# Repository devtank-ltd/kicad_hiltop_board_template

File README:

Copyright Devtank Ltd 2022.

This documentation describes Open Hardware and is Licensed under CERN-OHL-W v2.

You may redistribute and modify this documentation under the terms of the CERN-OHL-W v2 (https://cern.ch/cern-ohl). This documentation is distributed WITHOUT ANY EXPRESS OR IMPLIED WARRANTY, INCLUDING OF MERCHANTABILITY, SATISFACTORY QUALITY AND FITNESS FOR A PARTICULAR PURPOSE. Please see the CERN-OHL-W v2 for applicable conditions

Source location: git@github.com:devtank-ltd/hiltop_motherboard.git 

As per CERN-OHL-W v2 section 4.1, should You produce hardware based on these sources, You must maintain the   Source Location visible on the external case of the HILTOP or other product you make using this documentation.

This folder contains a reference HILTOP plug-in card design schematics & PCB layout. You may use this design as a starting template for developing new plug-in modules for HILTOP.

You will need Kicad to open hardware design files.

HILTOP products and other test and measurement solutions can be purchased directly from Devtank Ltd.

Please contact:
Tim Telford
CTO - Devtank Ltd
+44 (0)1332 650944

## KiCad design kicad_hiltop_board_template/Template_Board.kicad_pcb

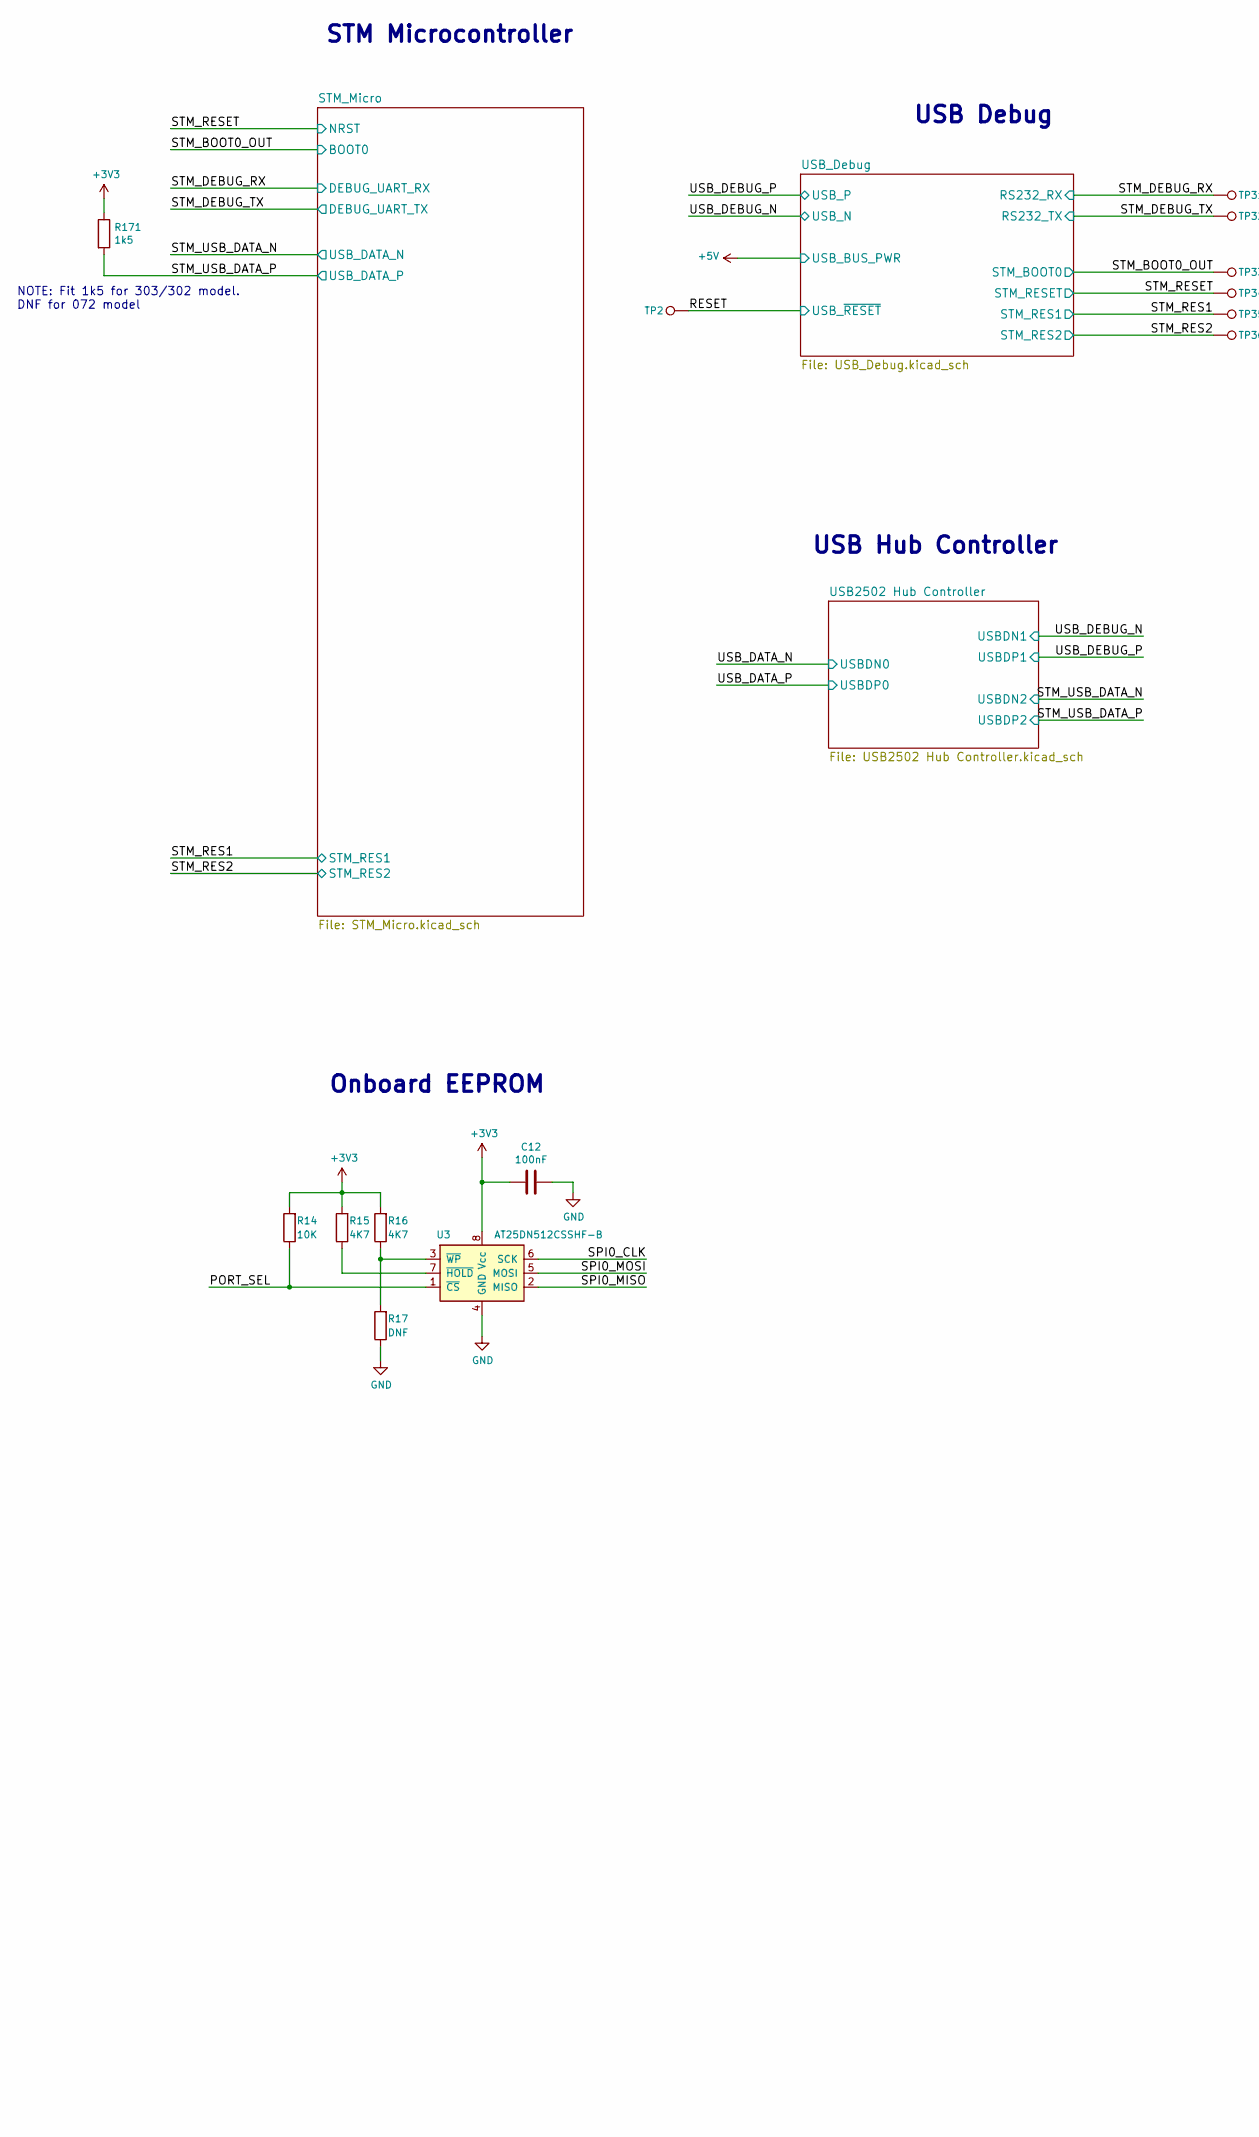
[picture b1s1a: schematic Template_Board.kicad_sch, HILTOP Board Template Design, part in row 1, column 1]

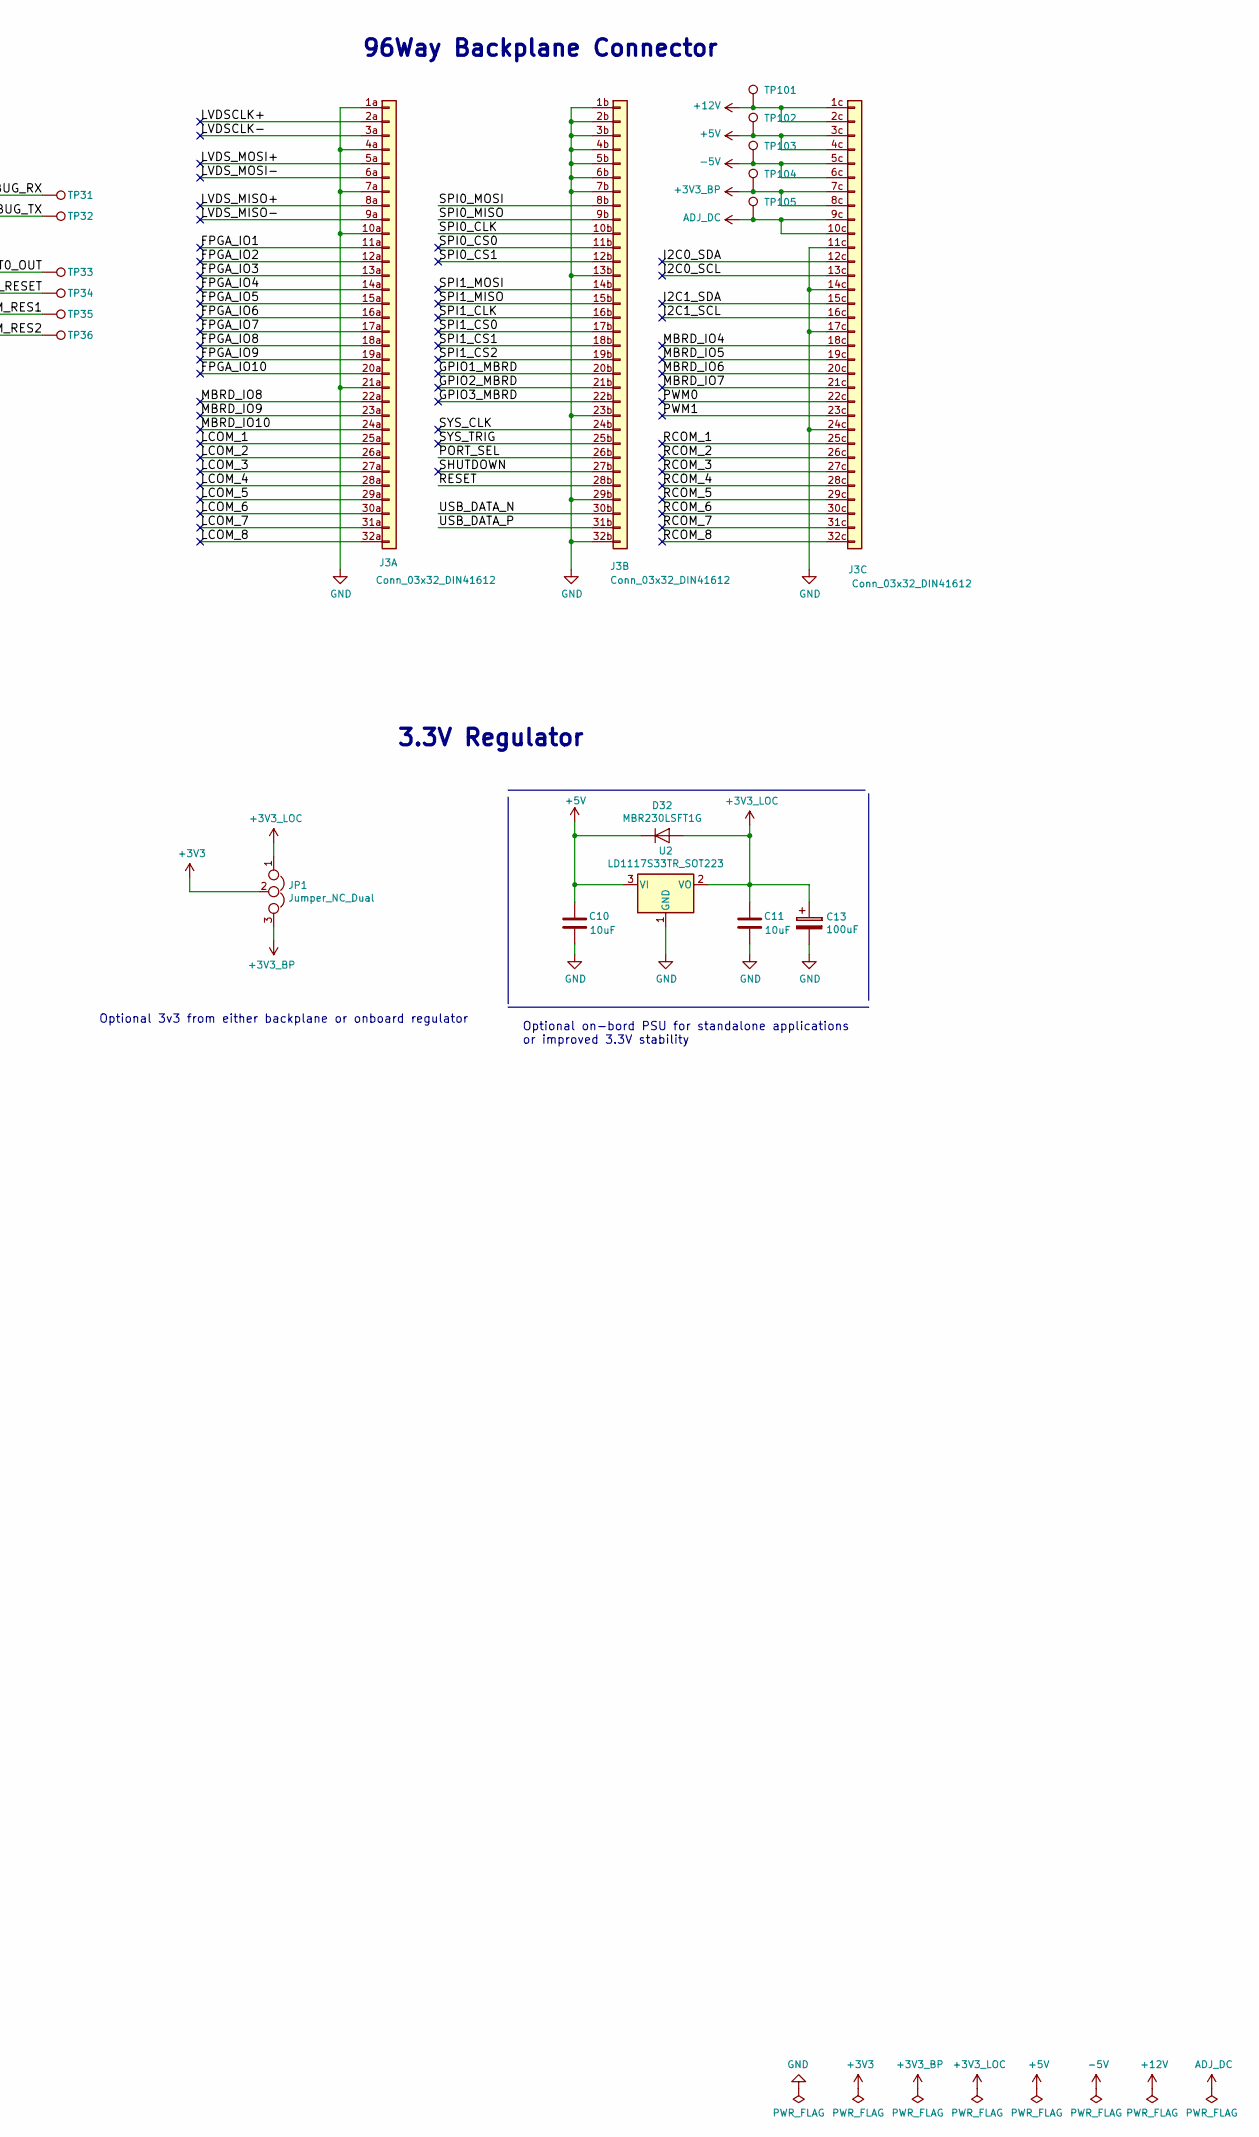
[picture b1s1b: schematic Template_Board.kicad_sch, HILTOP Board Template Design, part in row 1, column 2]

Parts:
C10, C11: 10uF; C_0805_2012Metric
C12: 100nF; C_0402_1005Metric
C13: 100uF; CP_Elec_6.3x7.7
D32: MBR230LSFT1G; D_SOD-123
J3: Conn_03x32_DIN41612; Socket_DIN41612-CaseC1-full-Male-96Pin-3rows_correct
JP1: Jumper_NC_Dual; PinHeader_1x03_P2.54mm_Vertical
R14: 10K; R_0603_1608Metric
R15, R16: 4K7; R_0603_1608Metric
R17: DNF; R_0603_1608Metric
R171: 1k5; R_0603_1608Metric
TP2, TP31, TP32, TP33, TP34, TP35, TP36, TP101, TP102, TP103, TP104, TP105: Test_Point; TestPoint_THTPad_D1.0mm_Drill0.5mm
U2: LD1117S33TR_SOT223; SOT-223-3_TabPin2
U3: AT25DN512CSSHF-B; SOIC-8_3.9x4.9mm_P1.27mm

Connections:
+3V3: C12.2, JP1.2, R14.2, R15.2, R16.2, R171.1, U3.8 (Vcc); also elsewhere on the board
+3V3_BP: J3.7c (Pin_7), J3.8c (Pin_8), JP1.3, TP104.1
+3V3_LOC: C11.2, C13.1, D32.2 (A), JP1.1, U2.2 (VO)
+5V: C10.2, D32.1 (K), J3.3c (Pin_3), J3.4c (Pin_4), TP102.1, U2.3 (VI); also elsewhere on the board
+12V: J3.1c (Pin_1), J3.2c (Pin_2), TP101.1
-5V: J3.5c (Pin_5), J3.6c (Pin_6), TP103.1
/FPGA_IO1: J3.11a (Pin_11)
/FPGA_IO2: J3.12a (Pin_12)
/FPGA_IO3: J3.13a (Pin_13)
/FPGA_IO4: J3.14a (Pin_14)
/FPGA_IO5: J3.15a (Pin_15)
/FPGA_IO6: J3.16a (Pin_16)
/FPGA_IO7: J3.17a (Pin_17)
/FPGA_IO8: J3.18a (Pin_18)
/FPGA_IO9: J3.19a (Pin_19)
/FPGA_IO10: J3.20a (Pin_20)
/GPIO1_MBRD: J3.20b (Pin_20)
/GPIO2_MBRD: J3.21b (Pin_21)
/GPIO3_MBRD: J3.22b (Pin_22)
/I2C0_SCL: J3.13c (Pin_13)
/I2C0_SDA: J3.12c (Pin_12)
/I2C1_SCL: J3.16c (Pin_16)
/I2C1_SDA: J3.15c (Pin_15)
/LCOM_1: J3.25a (Pin_25)
/LCOM_2: J3.26a (Pin_26)
/LCOM_3: J3.27a (Pin_27)
/LCOM_4: J3.28a (Pin_28)
/LCOM_5: J3.29a (Pin_29)
/LCOM_6: J3.30a (Pin_30)
/LCOM_7: J3.31a (Pin_31)
/LCOM_8: J3.32a (Pin_32)
/LVDSCLK+: J3.2a (Pin_2)
/LVDSCLK-: J3.3a (Pin_3)
/LVDS_MISO+: J3.8a (Pin_8)
/LVDS_MISO-: J3.9a (Pin_9)
/LVDS_MOSI+: J3.5a (Pin_5)
/LVDS_MOSI-: J3.6a (Pin_6)
/MBRD_IO4: J3.18c (Pin_18)
/MBRD_IO5: J3.19c (Pin_19)
/MBRD_IO6: J3.20c (Pin_20)
/MBRD_IO7: J3.21c (Pin_21)
/MBRD_IO8: J3.22a (Pin_22)
/MBRD_IO9: J3.23a (Pin_23)
/MBRD_IO10: J3.24a (Pin_24)
/PORT_SEL: J3.26b (Pin_26), R14.1, U3.1 (~CS)
/PWM0: J3.22c (Pin_22)
/PWM1: J3.23c (Pin_23)
/RCOM_1: J3.25c (Pin_25)
/RCOM_2: J3.26c (Pin_26)
/RCOM_3: J3.27c (Pin_27)
/RCOM_4: J3.28c (Pin_28)
/RCOM_5: J3.29c (Pin_29)
/RCOM_6: J3.30c (Pin_30)
/RCOM_7: J3.31c (Pin_31)
/RCOM_8: J3.32c (Pin_32)
/RESET: J3.28b (Pin_28), TP2.1; also elsewhere on the board
/SHUTDOWN: J3.27b (Pin_27)
/SPI0_CLK: J3.10b (Pin_10), U3.6 (SCK)
/SPI0_CS0: J3.11b (Pin_11)
/SPI0_CS1: J3.12b (Pin_12)
/SPI0_MISO: J3.9b (Pin_9), U3.2 (MISO)
/SPI0_MOSI: J3.8b (Pin_8), U3.5 (MOSI)
/SPI1_CLK: J3.16b (Pin_16)
/SPI1_CS0: J3.17b (Pin_17)
/SPI1_CS1: J3.18b (Pin_18)
/SPI1_CS2: J3.19b (Pin_19)
/SPI1_MISO: J3.15b (Pin_15)
/SPI1_MOSI: J3.14b (Pin_14)
/STM_BOOT0_OUT: TP33.1; also elsewhere on the board
/STM_DEBUG_RX: TP31.1; also elsewhere on the board
/STM_DEBUG_TX: TP32.1; also elsewhere on the board
/STM_RES1: TP35.1; also elsewhere on the board
/STM_RES2: TP36.1; also elsewhere on the board
/STM_RESET: TP34.1; also elsewhere on the board
/STM_USB_DATA_P: R171.2; also elsewhere on the board
/SYS_CLK: J3.24b (Pin_24)
/SYS_TRIG: J3.25b (Pin_25)
/USB_DATA_N: J3.30b (Pin_30); also elsewhere on the board
/USB_DATA_P: J3.31b (Pin_31); also elsewhere on the board
ADJ_DC: J3.9c (Pin_9), J3.10c (Pin_10), TP105.1
GND: C10.1, C11.1, C12.1, C13.2, J3.1a (Pin_1), J3.1b (Pin_1), J3.2b (Pin_2), J3.3b (Pin_3), J3.4a (Pin_4), J3.4b (Pin_4), J3.5b (Pin_5), J3.6b (Pin_6), J3.7a (Pin_7), J3.7b (Pin_7), J3.10a (Pin_10), J3.11c (Pin_11), J3.13b (Pin_13), J3.14c (Pin_14), J3.17c (Pin_17), J3.21a (Pin_21), J3.23b (Pin_23), J3.24c (Pin_24), J3.29b (Pin_29), J3.32b (Pin_32), R17.1, U2.1 (GND), U3.4 (GND); also elsewhere on the board
unnamed: R15.1, U3.7 (~HOLD)
unnamed: R16.1, R17.2, U3.3 (~WP)

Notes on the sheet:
USB Debug
96Way Backplane Connector
Optional on-bord PSU for standalone applications or improved 3.3V stability
Onboard EEPROM
USB Hub Controller
NOTE: Fit 1k5 for 303/302 model. DNF for 072 model
STM Microcontroller
Optional 3v3 from either backplane or onboard regulator
3.3V Regulator

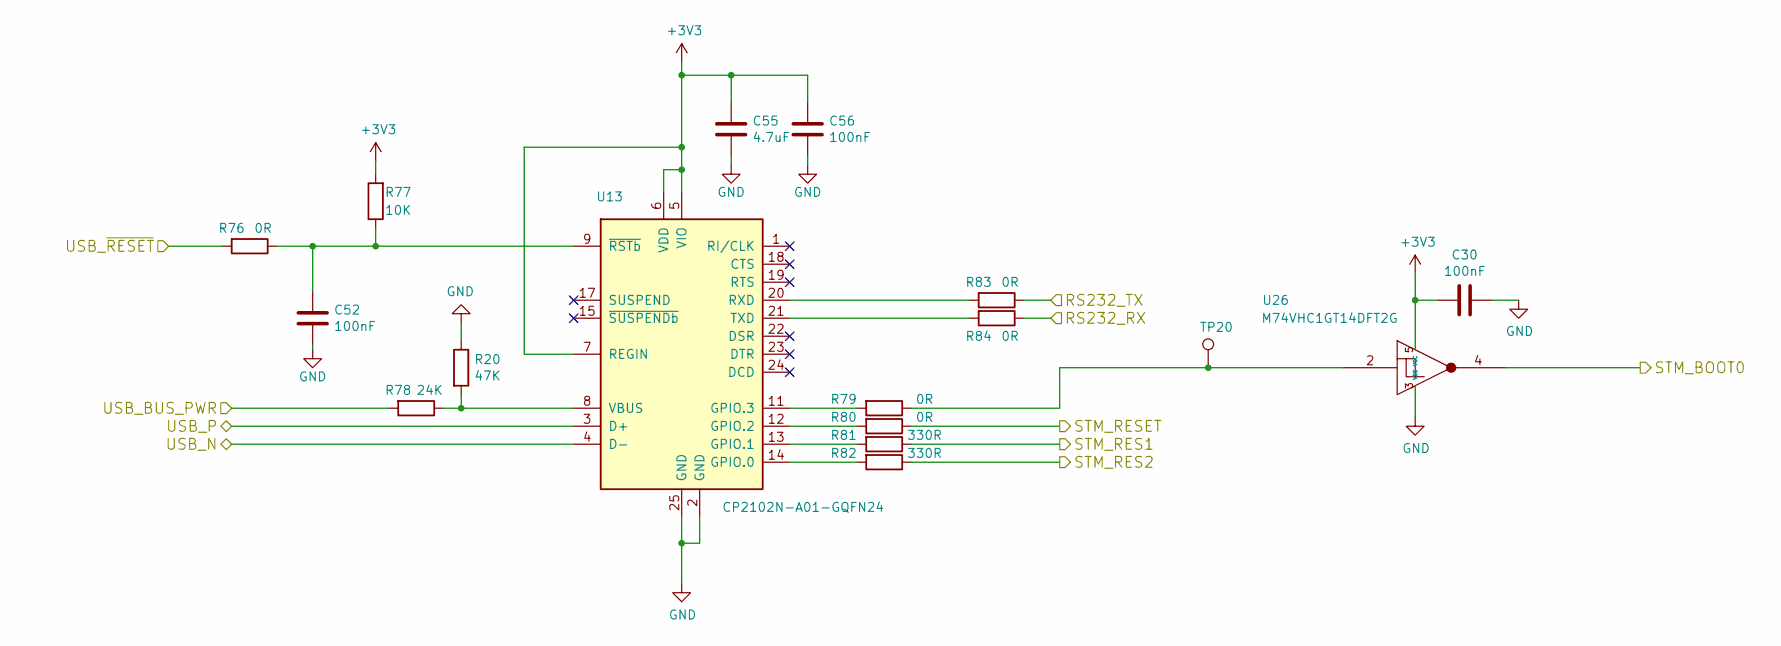
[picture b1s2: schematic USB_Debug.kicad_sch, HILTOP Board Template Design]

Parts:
C30, C56: 100nF; C_0402_1005Metric
C52: 100nF; C_0603_1608Metric
C55: 4.7uF; C_0402_1005Metric; Voltage 6.3V
R20: 47K; R_0603_1608Metric
R76, R79, R80, R83, R84: 0R; R_0603_1608Metric
R77: 10K; R_0603_1608Metric
R78: 24K; R_0603_1608Metric
R81, R82: 330R; R_0603_1608Metric
TP20: Test_Point; TestPoint_THTPad_D1.0mm_Drill0.5mm
U13: CP2102N-A01-GQFN24; CP2102_QFN-24-1EP_4x4mm_P0.5mm_EP2.6x2.6mm_ThermalVias_0.3m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
U26: M74VHC1GT14DFT2G; SOT-353_SC-70-5

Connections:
+3V3: C30.2, C55.1, C56.1, R77.2, U13.5 (VIO), U13.6 (VDD), U13.7 (REGIN), U26.5 (VCC); also elsewhere on the board
+5V: R78.2; also elsewhere on the board
/RESET: R76.2; also elsewhere on the board
/STM_BOOT0_OUT: U26.4; also elsewhere on the board
/STM_DEBUG_RX: R84.1; also elsewhere on the board
/STM_DEBUG_TX: R83.1; also elsewhere on the board
/STM_RES1: R81.1; also elsewhere on the board
/STM_RES2: R82.1; also elsewhere on the board
/STM_RESET: R80.1; also elsewhere on the board
/USB_DEBUG_N: U13.4 (D-); also elsewhere on the board
/USB_DEBUG_P: U13.3 (D+); also elsewhere on the board
GND: C30.1, C52.2, C55.2, C56.2, R20.1, U13.2 (GND), U13.25 (GND), U26.3 (VSS); also elsewhere on the board
unnamed: C52.1, R76.1, R77.1, U13.9 (~RSTb)
unnamed: R20.2, R78.1, U13.8 (VBUS)
unnamed: R79.1, TP20.1, U26.2
unnamed: R79.2, U13.11 (GPIO.3)
unnamed: R80.2, U13.12 (GPIO.2)
unnamed: R81.2, U13.13 (GPIO.1)
unnamed: R82.2, U13.14 (GPIO.0)
unnamed: R83.2, U13.20 (RXD)
unnamed: R84.2, U13.21 (TXD)

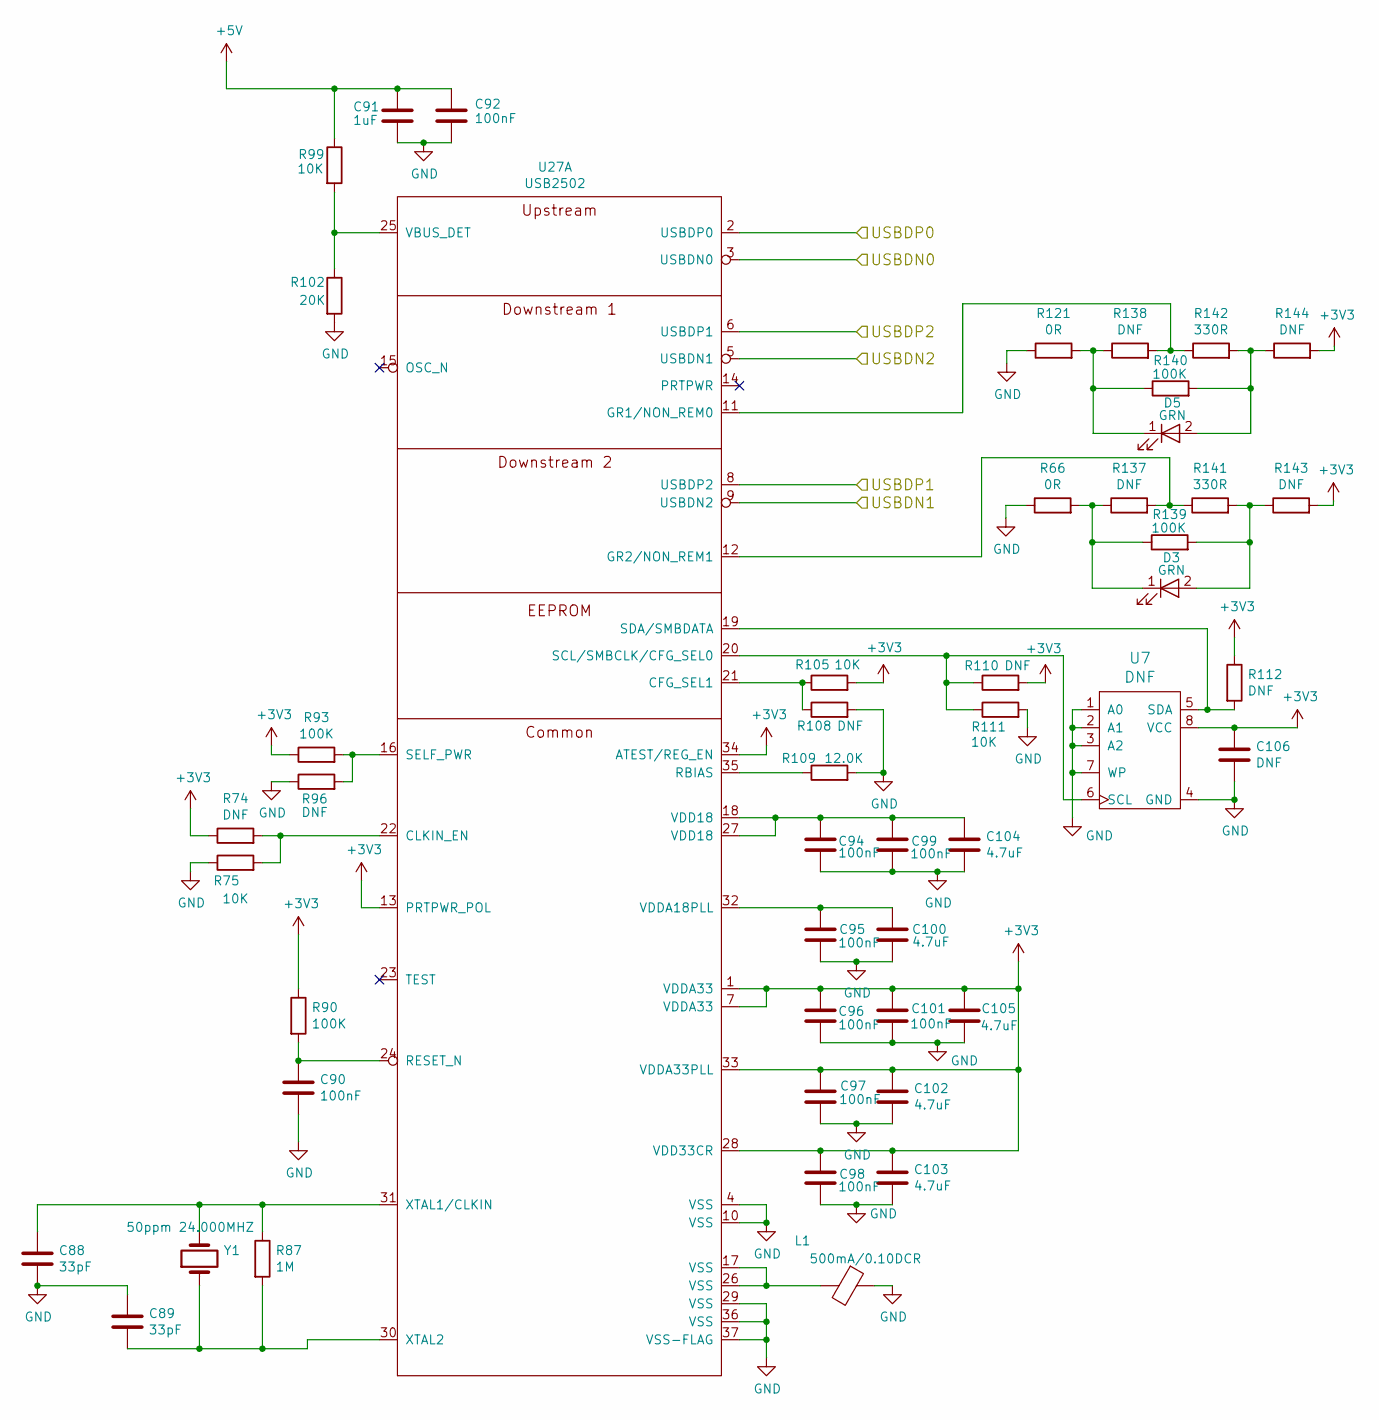
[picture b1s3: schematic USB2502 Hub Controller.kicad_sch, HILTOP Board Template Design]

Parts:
C88, C89: 33pF; C_0603_1608Metric
C90: 100nF; C_0603_1608Metric
C91: 1uF; C_0402_1005Metric; Voltage 16V
C92, C94, C95, C96, C97, C98, C99, C101: 100nF; C_0402_1005Metric
C100, C102, C103, C104, C105: 4.7uF; C_0402_1005Metric; Voltage 6.3V
C106: DNF; C_0402_1005Metric
D3, D5: GRN; LED_0603_1608Metric
L1: 500mA/0.10DCR; L_0805_2012Metric
R66, R121: 0R; R_0603_1608Metric
R74, R96, R108, R110, R112, R137, R138, R143, R144: DNF; R_0603_1608Metric
R75, R99, R105, R111: 10K; R_0603_1608Metric
R87: 1M; R_0603_1608Metric
R90, R93, R139, R140: 100K; R_0603_1608Metric
R102: 20K; R_0603_1608Metric
R109: 12.0K; R_0603_1608Metric; Tolerance 1%
R141, R142: 330R; R_0603_1608Metric
U7: DNF; SOIC-8_3.9x4.9mm_P1.27mm
U27: USB2502; QFN-36-1EP_6x6mm_P0.5mm_EP3.7x3.7mm
Y1: 50ppm 24.000MHZ; Crystal_SMD_TXC_7A-2Pin_5x3.2mm

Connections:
+3V3: C96.1, C97.1, C98.1, C101.1, C102.1, C103.1, C105.1, C106.1, R74.1, R90.1, R93.1, R105.2, R110.2, R112.1, R143.2, R144.2, U7.8 (VCC), U27.1 (VDDA33), U27.7 (VDDA33), U27.13 (PRTPWR_POL), U27.28 (VDD33CR), U27.33 (VDDA33PLL), U27.34 (ATEST/REG_EN); also elsewhere on the board
+5V: C91.1, C92.1, R99.1; also elsewhere on the board
/STM_USB_DATA_N: U27.5 (USBDN1); also elsewhere on the board
/STM_USB_DATA_P: U27.6 (USBDP1); also elsewhere on the board
/USB_DATA_N: U27.3 (USBDN0); also elsewhere on the board
/USB_DATA_P: U27.2 (USBDP0); also elsewhere on the board
/USB_DEBUG_N: U27.9 (USBDN2); also elsewhere on the board
/USB_DEBUG_P: U27.8 (USBDP2); also elsewhere on the board
GND: C88.2, C89.1, C90.2, C91.2, C92.2, C94.2, C95.2, C96.2, C97.2, C98.2, C99.2, C100.2, C101.2, C102.2, C103.2, C104.2, C105.2, C106.2, L1.1, R66.1, R75.1, R96.1, R102.2, R108.2, R109.2, R111.2, R121.1, U7.1 (A0), U7.2 (A1), U7.3 (A2), U7.4 (GND), U7.7 (WP), U27.4 (VSS), U27.10 (VSS), U27.29 (VSS), U27.36 (VSS), U27.37 (VSS-FLAG); also elsewhere on the board
unnamed: C88.1, R87.1, U27.31 (XTAL1/CLKIN), Y1.2
unnamed: C89.2, R87.2, U27.30 (XTAL2), Y1.1
unnamed: C90.1, R90.2, U27.24 (RESET_N)
unnamed: C95.1, C100.1, U27.32 (VDDA18PLL)
unnamed: C94.1, C99.1, C104.1, U27.18 (VDD18), U27.27 (VDD18)
unnamed: D3.1 (K), R66.2, R137.1, R139.1
unnamed: D3.2 (A), R139.2, R141.2, R143.1
unnamed: D5.1 (K), R121.2, R138.1, R140.1
unnamed: D5.2 (A), R140.2, R142.2, R144.1
unnamed: L1.2, U27.17 (VSS), U27.26 (VSS)
unnamed: R74.2, R75.2, U27.22 (CLKIN_EN)
unnamed: R93.2, R96.2, U27.16 (SELF_PWR)
unnamed: R99.2, R102.1, U27.25 (VBUS_DET)
unnamed: R105.1, R108.1, U27.21 (CFG_SEL1)
unnamed: R109.1, U27.35 (RBIAS)
unnamed: R110.1, R111.1, U7.6 (SCL), U27.20 (SCL/SMBCLK/CFG_SEL0)
unnamed: R112.2, U7.5 (SDA), U27.19 (SDA/SMBDATA)
unnamed: R137.2, R141.1, U27.12 (GR2/NON_REM1)
unnamed: R138.2, R142.1, U27.11 (GR1/NON_REM0)

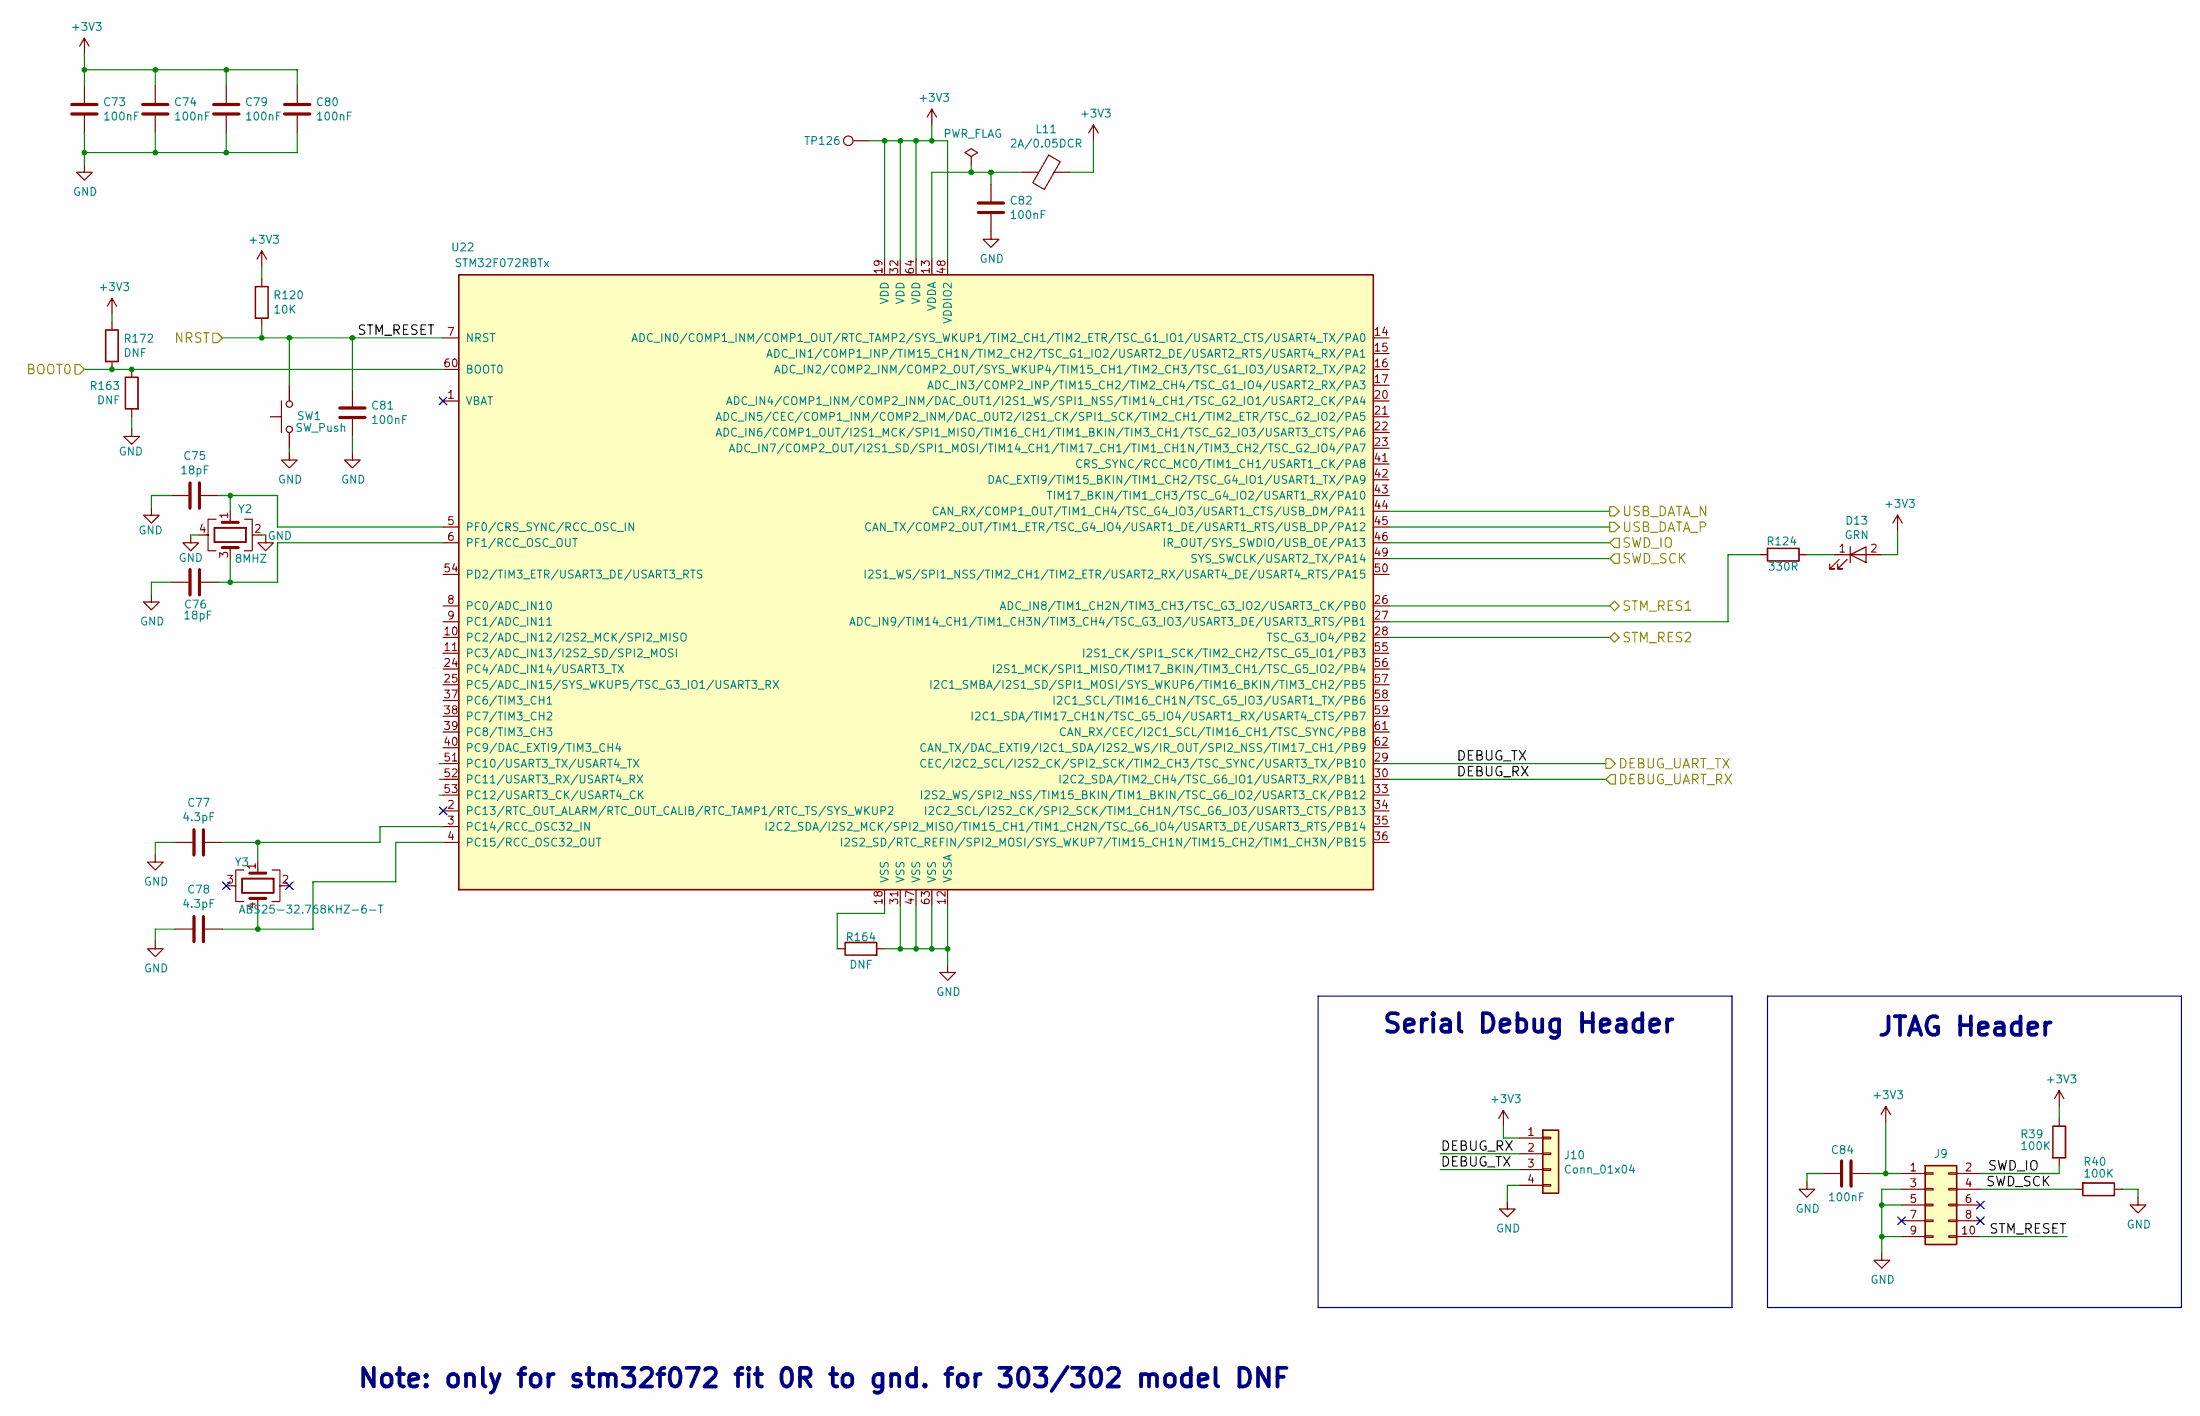
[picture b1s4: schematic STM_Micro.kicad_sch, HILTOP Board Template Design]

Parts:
C73, C74, C79, C80, C84: 100nF; C_0402_1005Metric
C75, C76: 18pF; C_0603_1608Metric
C77, C78: 4.3pF; C_0603_1608Metric
C81, C82: 100nF; C_0603_1608Metric
D13: GRN; LED_0603_1608Metric
J9: Conn_02x05_Odd_Even; PinHeader_2x05_P2.54mm_Vertical
J10: Conn_01x04; PinHeader_1x04_P1.27mm_Vertical
L11: 2A/0.05DCR; L_0805_2012Metric
R39, R40: 100K; R_0603_1608Metric
R120: 10K; R_0603_1608Metric
R124: 330R; R_0603_1608Metric
R163, R172: DNF; R_0603_1608Metric
R164: DNF; R_0402_1005Metric
SW1: SW_Push; SW_SPST_B3U-1000P
TP126: Test_Point; TestPoint_THTPad_D1.0mm_Drill0.5mm
U22: STM32F072RBTx; LQFP-64_10x10mm_P0.5mm
Y2: 8MHZ; Crystal_SMD_Abracon_ABM3C-4Pin_5.0x3.2mm
Y3: ABS25-32.768KHZ-6-T; Crystal_SMD_7050-4Pin_7.0x5.0mm

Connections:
+3V3: C73.1, C74.1, C79.1, C80.1, C84.2, D13.2 (A), J9.1, J10.1, L11.1, R39.1, R120.1, R172.1, TP126.1, U22.19 (VDD), U22.32 (VDD), U22.48 (VDDIO2), U22.64 (VDD); also elsewhere on the board
/STM_BOOT0_OUT: R163.1, R172.2, U22.60 (BOOT0); also elsewhere on the board
/STM_DEBUG_RX: J10.2, U22.30 (I2C2_SDA/TIM2_CH4/TSC_G6_IO1/USART3_RX/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); also elsewhere on the board
/STM_DEBUG_TX: J10.3, U22.29 (CEC/I2C2_SCL/I2S2_CK/SPI2_SCK/TIM2_CH3/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); also elsewhere on the board
/STM_Micro/SWD_IO: J9.2, R39.2, U22.46 (IR_OUT/SYS_SWDIO/USB_OE/PA13)
/STM_Micro/SWD_SCK: J9.4, R40.2, U22.49 (SYS_SWCLK/USART2_TX/PA14)
/STM_RES1: U22.26 (ADC_IN8/TIM1_CH2N/TIM3_CH3/TSC_G3_IO2/U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); also elsewhere on the board
/STM_RES2: U22.28 (TSC_G3_IO4/PB2); also elsewhere on the board
/STM_RESET: C81.1, J9.10, R120.2, SW1.2, U22.7 (NRST); also elsewhere on the board
/STM_USB_DATA_N: U22.44 (CAN_RX/COMP1_OUT/TIM1_CH4/TSC_G4_IO3/US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); also elsewhere on the board
/STM_USB_DATA_P: U22.45 (CAN_TX/COMP2_OUT/TIM1_ETR/TSC_G4_IO4/US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); also elsewhere on the board
GND: C73.2, C74.2, C75.2, C76.2, C77.2, C78.2, C79.2, C80.2, C81.2, C82.2, C84.1, J9.3, J9.5, J9.9, J10.4, R40.1, R163.2, R164.2, SW1.1, U22.12 (VSSA), U22.31 (VSS), U22.47 (VSS), U22.63 (VSS), Y2.2, Y2.4; also elsewhere on the board
unnamed: C75.1, U22.5 (PF0/CRS_SYNC/RCC_OSC_IN), Y2.1
unnamed: C76.1, U22.6 (PF1/RCC_OSC_OUT), Y2.3
unnamed: C77.1, U22.3 (PC14/RCC_OSC32_IN), Y3.1
unnamed: C78.1, U22.4 (PC15/RCC_OSC32_OUT), Y3.4
unnamed: C82.1, L11.2, U22.13 (VDDA)
unnamed: D13.1 (K), R124.1
unnamed: R124.2, U22.27 (ADC_IN9/TIM14_CH1/TIM1_CH3N/TIM3_CH4/TS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)
unnamed: R164.1, U22.18 (VSS)

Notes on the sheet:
JTAG Header
Note: only for stm32f072 fit 0R to gnd. for 303/302 model DNF
Serial Debug Header

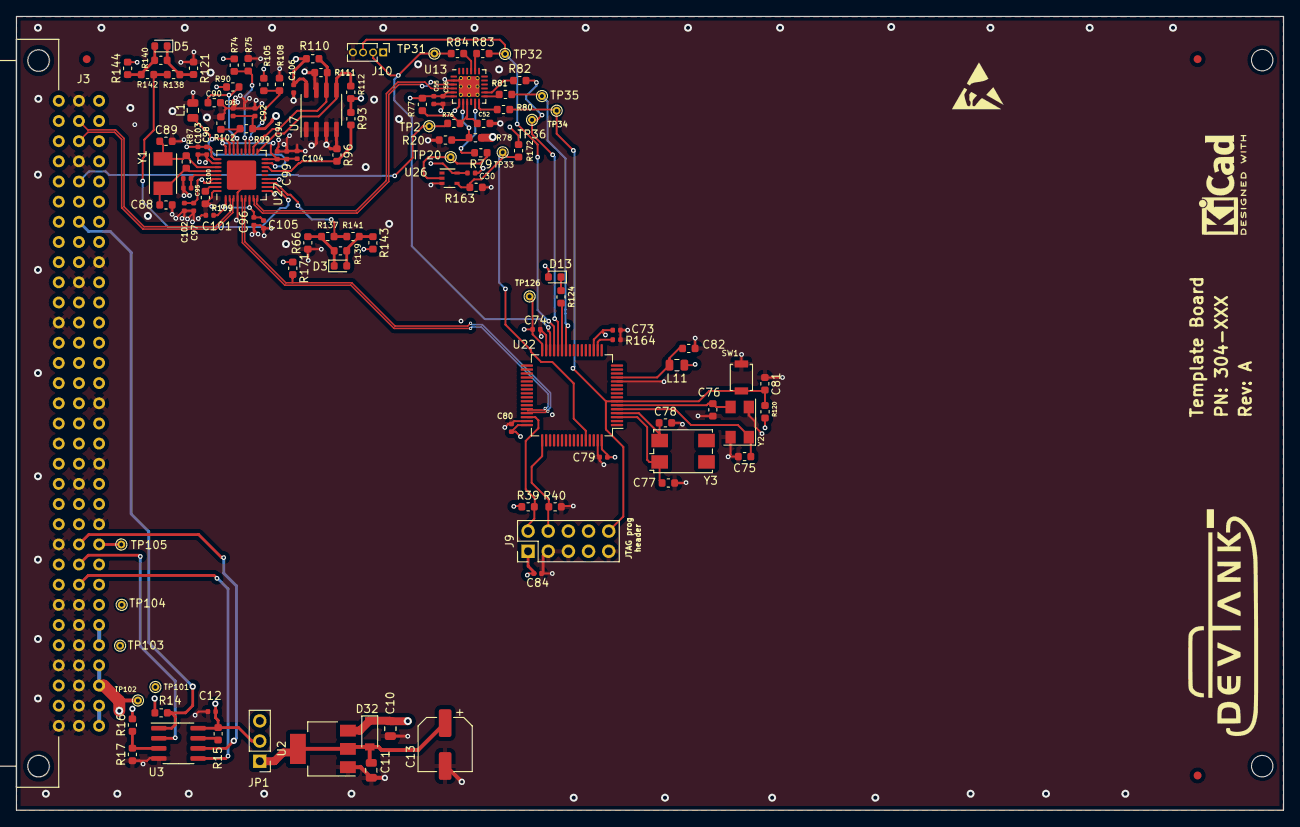
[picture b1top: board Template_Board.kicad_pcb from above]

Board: 4 copper layers, 159.6 x 100.0 mm, 118 parts (0 on the bottom side), 65 nets.

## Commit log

2022-11-03 Added new hiltop template design for new card development
2022-11-03 added readme and license files

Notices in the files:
kicad_hiltop_board_template/Template_Board.kicad_pcb:
(c) Copyright 2022 Devtank Ltd
Licensed under CERN-OHL-W V2.0
https://cern-ohl.web.cern.ch
